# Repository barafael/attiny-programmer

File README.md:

# attiny-programmer

A PCB board to use an Arduino Uno for burning programs to an AVR attiny85 8-pin microcontroller

## What it does

You can use this Arduino shield to program your attiny chip with a regular Arduino Uno.

To test if it works, you can try the standard blink sketch using pin 2 - that is connected to pin 13
of the UNO, which has an LED.

## Preparations

* Follow the steps from [here](http://highlowtech.org/?p=1695) and [here](http://highlowtech.org/?p=1706) to install support for your attiny85 in your Arduino IDE
* Solder appropriate headers and the 10uF capacitor to the shield
* Make sure you have selected the standard Arduino IDE presets for the Arduino Uno (Board: Arduino/Genuino Uno, Programmer: AVRISP mkII)
* Select the sketch ```File -> Examples -> ArduinoISP``` and burn it to your Uno
* Attach the shield
* Switch to the attiny board and your appropriate processor (like attiny85) in your IDE
* Switch your programmer to 'Arduino as ISP'
* You are now ready to write your attiny85 program to your chip!

## Circuit

Based on the circuit [here](http://highlowtech.org/?p=1706). You can either
bridge the gaps to have a permanent connection to the Arduino Uno, or you can
solder 2.54'' switches to toggle between the programmer and the output row.

## PCB

## Note

If your attiny85 becomes very hot, you inserted it the wrong way. It will still
work (mine did...) but don't test this too often!

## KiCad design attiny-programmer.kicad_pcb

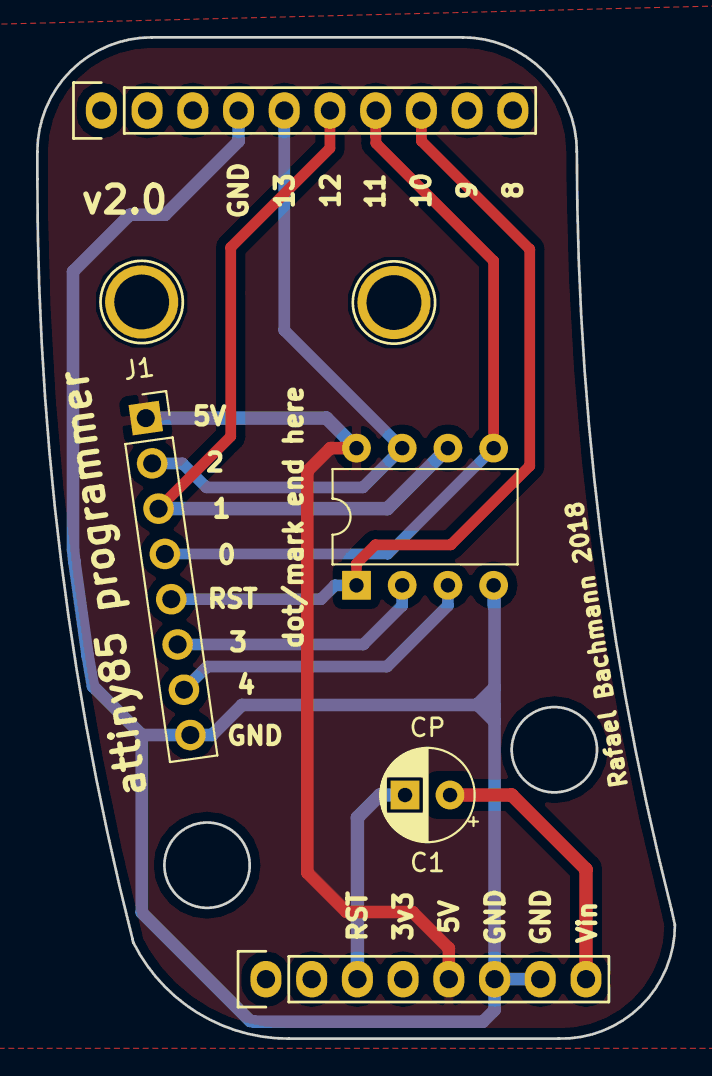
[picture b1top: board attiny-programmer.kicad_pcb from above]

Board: 2 copper layers, 35.4 x 55.6 mm, 7 parts (0 on the bottom side), 10 nets.

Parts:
C1: CP; CP_Radial_D5.0mm_P2.50mm
J1: Conn_01x08; PinSocket_1x08_P2.54mm_Vertical
P1: Power; Socket_Strip_Arduino_1x08
P3: Digital; Socket_Strip_Arduino_1x10
P7, P8: CONN_01X01; Arduino_1pin
U1: ATtiny85-20PU; DIP-8_W7.62mm

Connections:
+5V: J1.1, P1.5, U1.8
/10(**/SS): J1.5, P3.8, U1.1
/11(**/MOSI): J1.4, P3.7, U1.5
/12(MISO): J1.3, P3.6, U1.6
/13(SCK): J1.2, P3.5, U1.7
/Reset: C1.2, P1.3
/Vin: C1.1, P1.8
GND: J1.8, P1.6, P1.7, P3.4, U1.4
unnamed: J1.6, U1.2
unnamed: J1.7, U1.3

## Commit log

2018-01-12 add board fritzing file
2018-01-12 add pcb image
2018-01-12 Add instructions
2018-01-12 Add image of PCB to readme
2018-01-12 Add note about chip polarity
2018-01-13 Add real image of programmer
2018-01-13 Add photo
2018-01-13 more sleek board
2018-01-15 more sleeker board
2018-01-25 add circuit image
2018-01-31 Add programmer with assembled switches
2018-01-31 add note about switch pin spacing
2018-01-31 readme formatting
2018-06-29 remove more sharp edges
2018-06-29 new PCB image
2018-06-29 simplify PCB
2018-11-10 old version move
2018-11-10 add new kicad version
2018-11-10 add readme and images
2018-11-10 remove lines from schematic
